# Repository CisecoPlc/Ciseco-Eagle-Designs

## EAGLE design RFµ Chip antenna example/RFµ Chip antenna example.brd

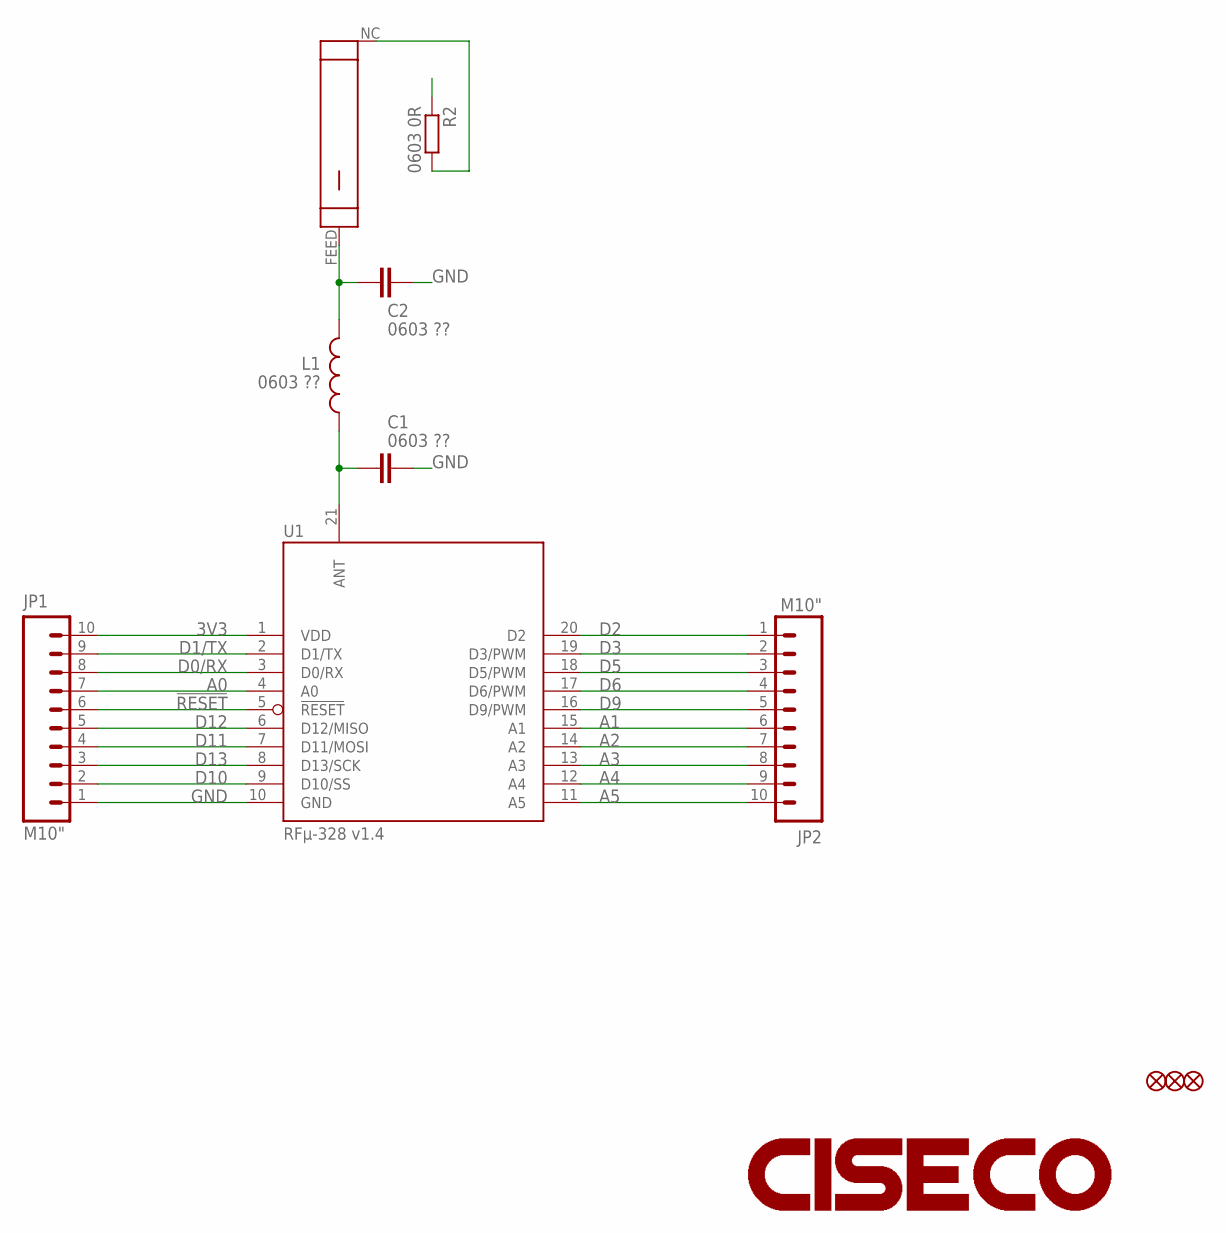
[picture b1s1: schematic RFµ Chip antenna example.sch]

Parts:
C1, C2: 0603 ??; C0603K-SMALL
JP1, JP2: M10"; 1X10
JP3, JP4, JP5: FIDUCIAL1X2.5-STOP; FIDUCIAL-1X2.5-STOP
L1: 0603 ??; C0603K-SMALL
LOGO1: CISECOLOGO-4MM; CISECO-4MM
R2: 0603 0R; C0603K-SMALL
U1: RFµ-328 v1.4; RFµ-LANDING-V2.0
U$1: JTICHIPANT

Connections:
3V3: JP1.10, U1.1 (VDD)
!RESET: JP1.6, U1.5 (!RESET)
A0: JP1.7, U1.4 (A0)
A1: JP2.6, U1.15 (A1)
A2: JP2.7, U1.14 (A2)
A3: JP2.8, U1.13 (A3)
A4: JP2.9, U1.12 (A4)
A5: JP2.10, U1.11 (A5)
ANT: C1.1, L1.1, U1.21 (ANT)
D0/RX: JP1.8, U1.3 (D0/RX)
D1/TX: JP1.9, U1.2 (D1/TX)
D2: JP2.1, U1.20 (D2)
D3: JP2.2, U1.19 (D3/PWM)
D5: JP2.3, U1.18 (D5/PWM)
D6: JP2.4, U1.17 (D6/PWM)
D9: JP2.5, U1.16 (D9/PWM)
D10: JP1.2, U1.9 (D10/SS)
D11: JP1.4, U1.7 (D11/MOSI)
D12: JP1.5, U1.6 (D12/MISO)
D13: JP1.3, U1.8 (D13/SCK)
GND: C1.2, C2.2, JP1.1, U1.10 (GND)
unnamed: C2.1, L1.2, U$1.FEED
unnamed: R2.2, U$1.NC

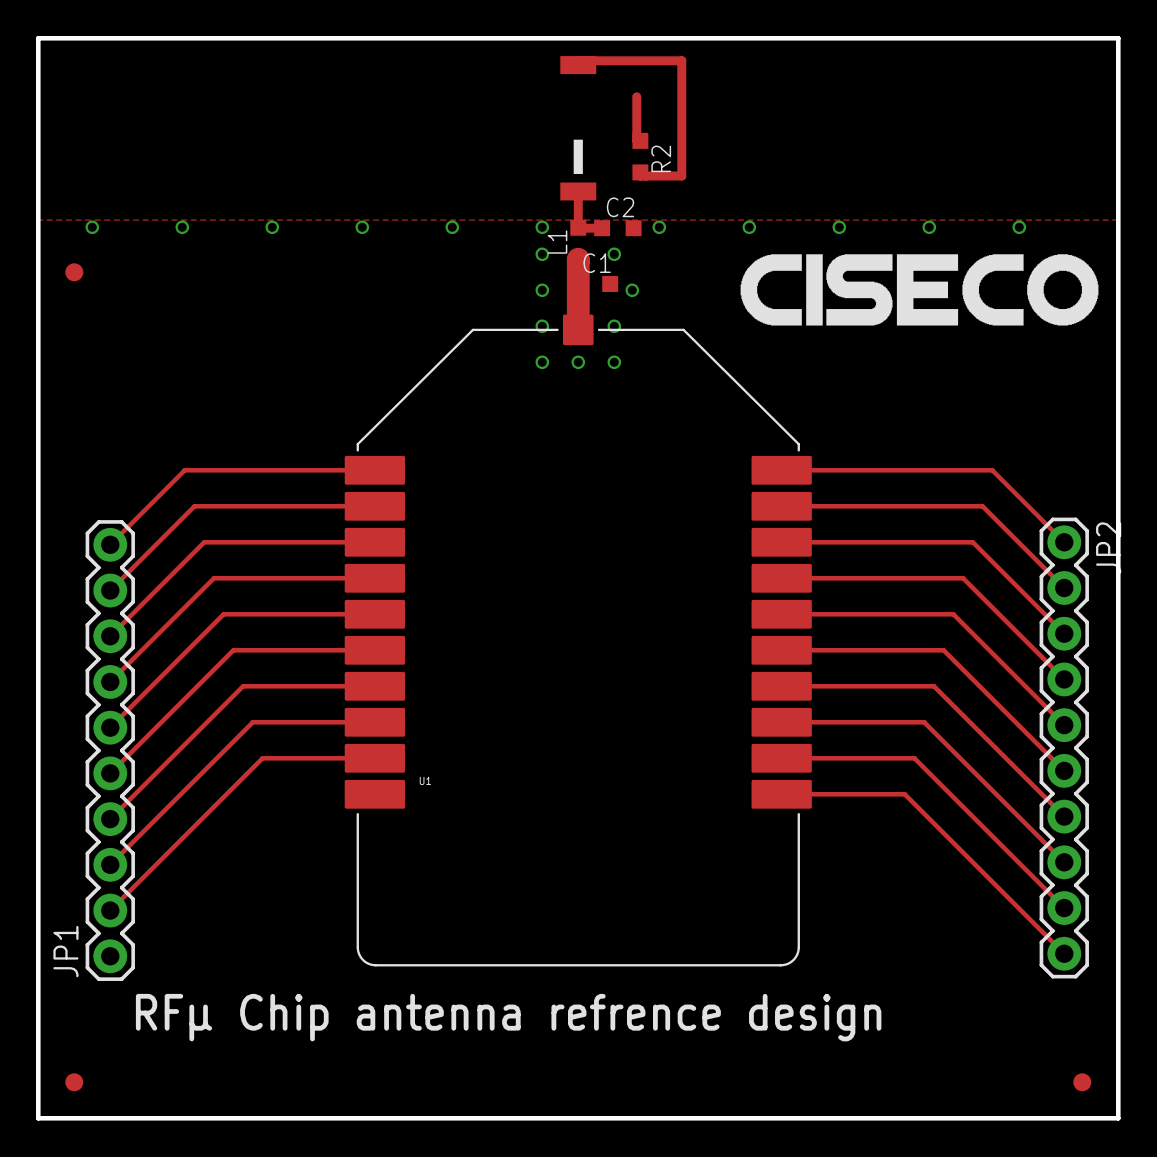
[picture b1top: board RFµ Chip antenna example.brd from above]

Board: 2 copper layers, 60.0 x 60.0 mm, 12 parts (0 on the bottom side), 23 nets.

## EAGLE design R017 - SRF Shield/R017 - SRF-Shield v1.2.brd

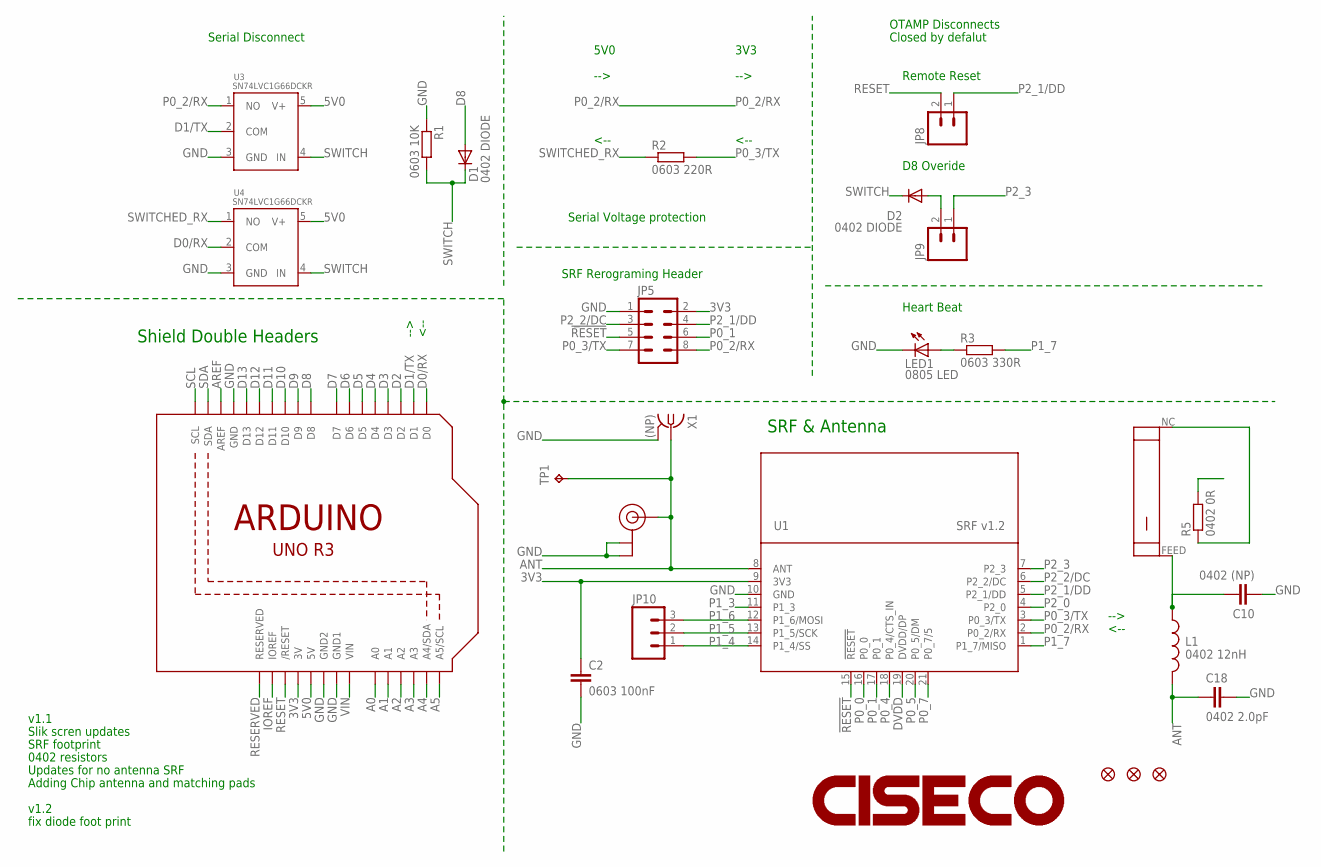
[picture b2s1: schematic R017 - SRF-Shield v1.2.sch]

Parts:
C2: 0603 100nF; C0402-SMALLER
C10: 0402 (NP); C0402-SMALLER
C18: 0402 2.0pF; C0402-SMALLER
D1, D2: 0402 DIODE; SOD88
JP4, JP6, JP7: FIDUCIAL1X2.5-STOP; FIDUCIAL-1X2.5-STOP
JP5: M04X2; 2X4
JP8, JP9: M02PTH; 1X02
JP10: M03PTH; 1X03
L1: 0402 12nH; C0402-SMALLER
LED1: 0805 LED; LED-0805-1206
R1: 0603 10K; R0402-SMALLER
R2: 0603 220R; R0402-SMALLER
R3: 0603 330R; R0402-SMALLER
R5: 0402 0R; R0402-SMALLER
TP1: TPPAD1-13; P1-13
U1: SRF v1.2; SRF-LANDING-NO-ANT-1.2
U2: ARDUINOR3-DOUBL-OFFSET; ARDUINOR3-DOUBLE-OFFSET
U3, U4: SN74LVC1G66DCKR; SC70
U5: U.FL (NP); U.FL
U6: JTICHIPANT; JTICHIPANT-ROT
U$3: CISECO-LARGE; CISECO-4MM
X1: (NP); J502-ND-142-0711-821/826-LWK1

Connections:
3V3: C2.1, JP5.2, U1.9 (3V3), U2.3V, U2.3V1 (3V)
5V0: U2.5V, U2.5V1 (5V), U3.5 (V+), U4.5 (V+)
!RESET: JP5.5, U1.15 (!RESET)
A0: U2.A0, U2.A6 (A0)
A1: U2.A1, U2.A7 (A1)
A2: U2.A2, U2.A8 (A2)
A3: U2.A3, U2.A9 (A3)
A4: U2.A4 (A4/SDA), U2.A10 (A4/SDA)
A5: U2.A5 (A5/SCL), U2.A11 (A5/SCL)
ANT: C18.1, L1.2, TP1.TP, U1.8 (ANT), U5.P$3 (SIGNAL), X1.1
AREF: U2.AREF, U2.AREF1 (AREF)
D0/RX: U2.D0, U2.D18 (D0), U4.2 (COM)
D1/TX: U2.D1, U2.D17 (D1), U3.2 (COM)
D2: U2.D2, U2.D16 (D2)
D3: U2.D3, U2.D15 (D3)
D4: U2.D4, U2.D14 (D4)
D5: U2.D5, U2.D19 (D5)
D6: U2.D6, U2.D20 (D6)
D7: U2.D7, U2.D21 (D7)
D8: D1.A, U2.D8, U2.D22 (D8)
D9: U2.D9, U2.D23 (D9)
D10: U2.D10, U2.D24 (D10)
D11: U2.D11, U2.D25 (D11)
D12: U2.D12, U2.D26 (D12)
D13: U2.D13, U2.D27 (D13)
DVDD: U1.19 (DVDD/DP)
GND: C2.2, C10.1, C18.2, JP5.1, LED1.C, R1.1, U1.10 (GND), U2.GND, U2.GND1, U2.GND2, U2.GND3 (GND1), U2.GND4 (GND2), U2.GND5 (GND), U3.3 (GND), U4.3 (GND), U5.P$1 (GND), U5.P$2 (GND), X1.G@1 (GND), X1.G@2 (GND), X1.G@3 (GND), X1.G@4 (GND)
IOREF: U2.IOREF, U2.IOREF1 (IOREF)
unnamed: LED1.A, R3.1
unnamed: C10.2, L1.1, U6.FEED
unnamed: R5.1, U6.NC
OTAMP_M: D2.A, JP9.2
P0_0: U1.16 (P0_0)
P0_1: JP5.6, U1.17 (P0_1)
P0_2/RX: JP5.8, U1.2 (P0_2/RX), U3.1 (NO)
P0_3/TX: JP5.7, R2.2, U1.3 (P0_3/TX)
P0_4: U1.18 (P0_4/CTS_IN)
P0_5: U1.20 (P0_5/DM)
P0_7: U1.21 (P0_7/5)
P1_3: U1.11 (P1_3)
P1_4: JP10.1, U1.14 (P1_4/SS)
P1_5: JP10.2, U1.13 (P1_5/SCK)
P1_6: JP10.3, U1.12 (P1_6/MOSI)
P1_7: R3.2, U1.1 (P1_7/MISO)
P2_0: U1.4 (P2_0)
P2_1/DD: JP5.4, JP8.1, U1.5 (P2_1/DD)
P2_2/DC: JP5.3, U1.6 (P2_2/DC)
P2_3: JP9.1, U1.7 (P2_3)
RESERVED: U2.RESERVED, U2.RESERVED1 (RESERVED)
RESET: JP8.2, U2.RESET (/RESET), U2.RESET1 (/RESET)
SCL: U2.SCL, U2.SCL1 (SCL)
SDA: U2.SDA, U2.SDA1 (SDA)
SWITCH: D1.C, D2.C, R1.2, U3.4 (IN), U4.4 (IN)
SWITCHED_RX: R2.1, U4.1 (NO)
VIN: U2.VIN, U2.VIN1 (VIN)

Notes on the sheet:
SRF Rerograming Header
5V0
3V3
Remote Reset
Heart Beat
Closed by defalut
OTAMP Disconnects
Serial Voltage protection
Serial Disconnect
<--
-->
D8 Overide
Shield Double Headers
SRF & Antenna
v1.1
Slik scren updates
SRF footprint
0402 resistors
Updates for no antenna SRF
Adding Chip antenna and matching pads
v1.2
fix diode foot print

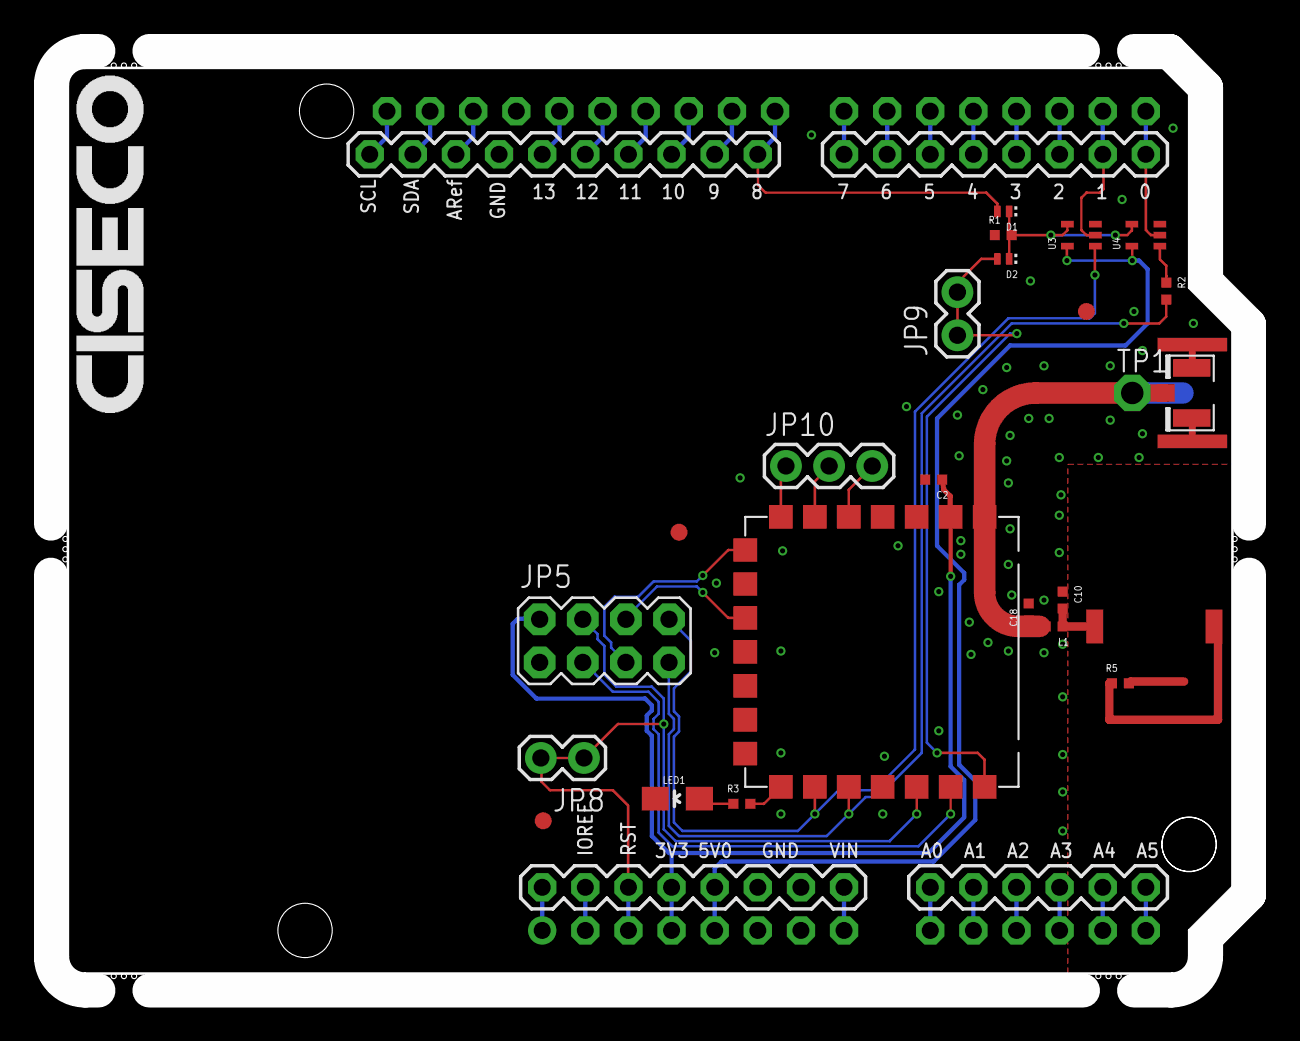
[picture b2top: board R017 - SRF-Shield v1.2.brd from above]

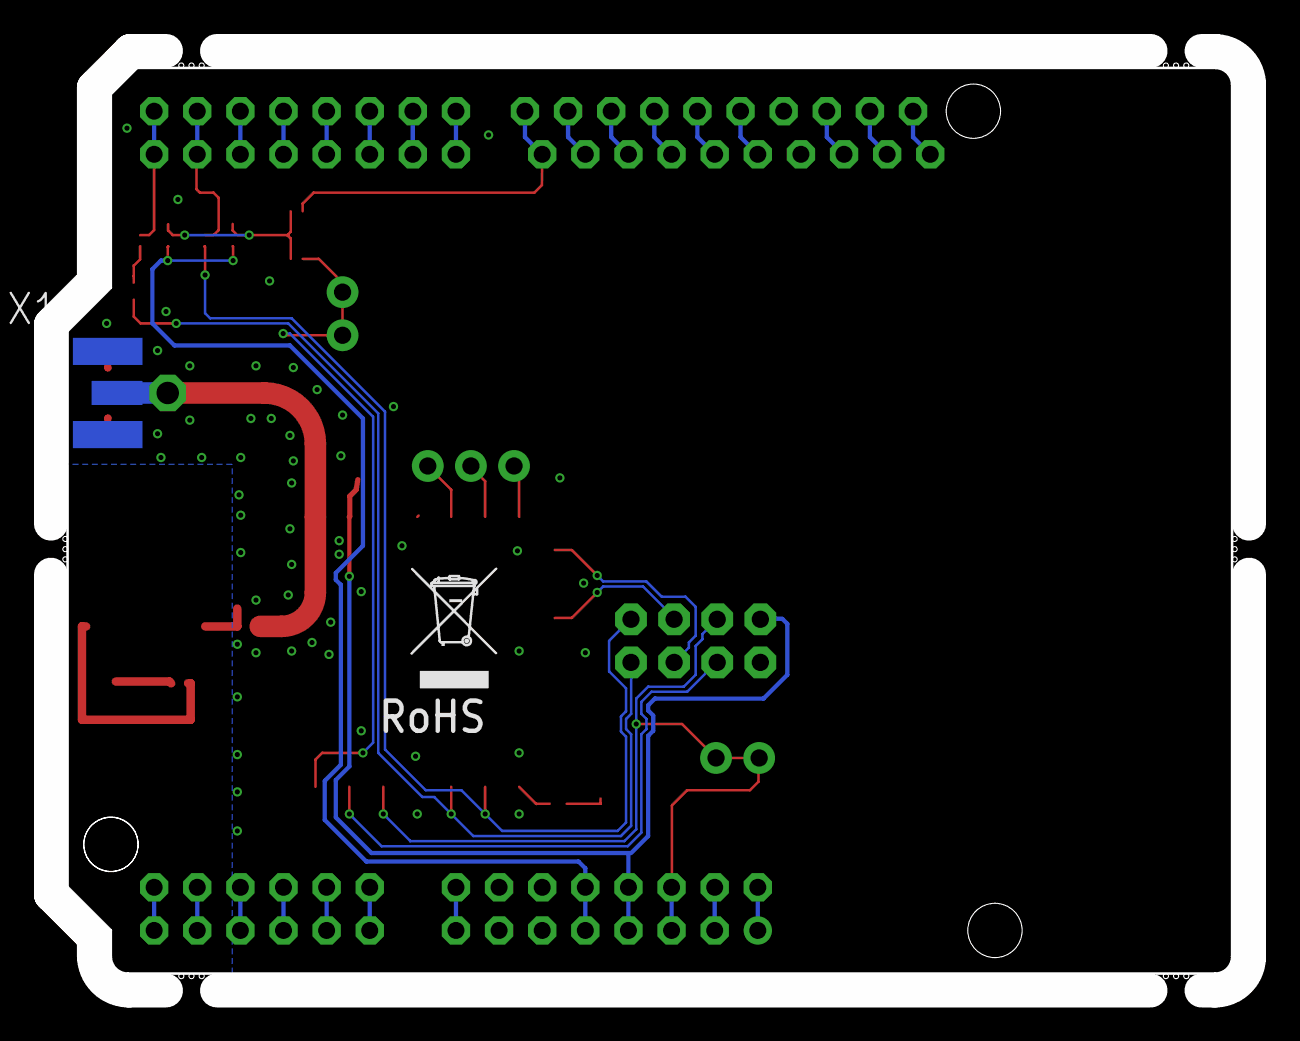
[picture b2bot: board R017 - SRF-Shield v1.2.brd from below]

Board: 2 copper layers, 70.6 x 55.4 mm, 28 parts (2 on the bottom side), 48 nets.

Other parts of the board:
U$6: WEEE-LOGO

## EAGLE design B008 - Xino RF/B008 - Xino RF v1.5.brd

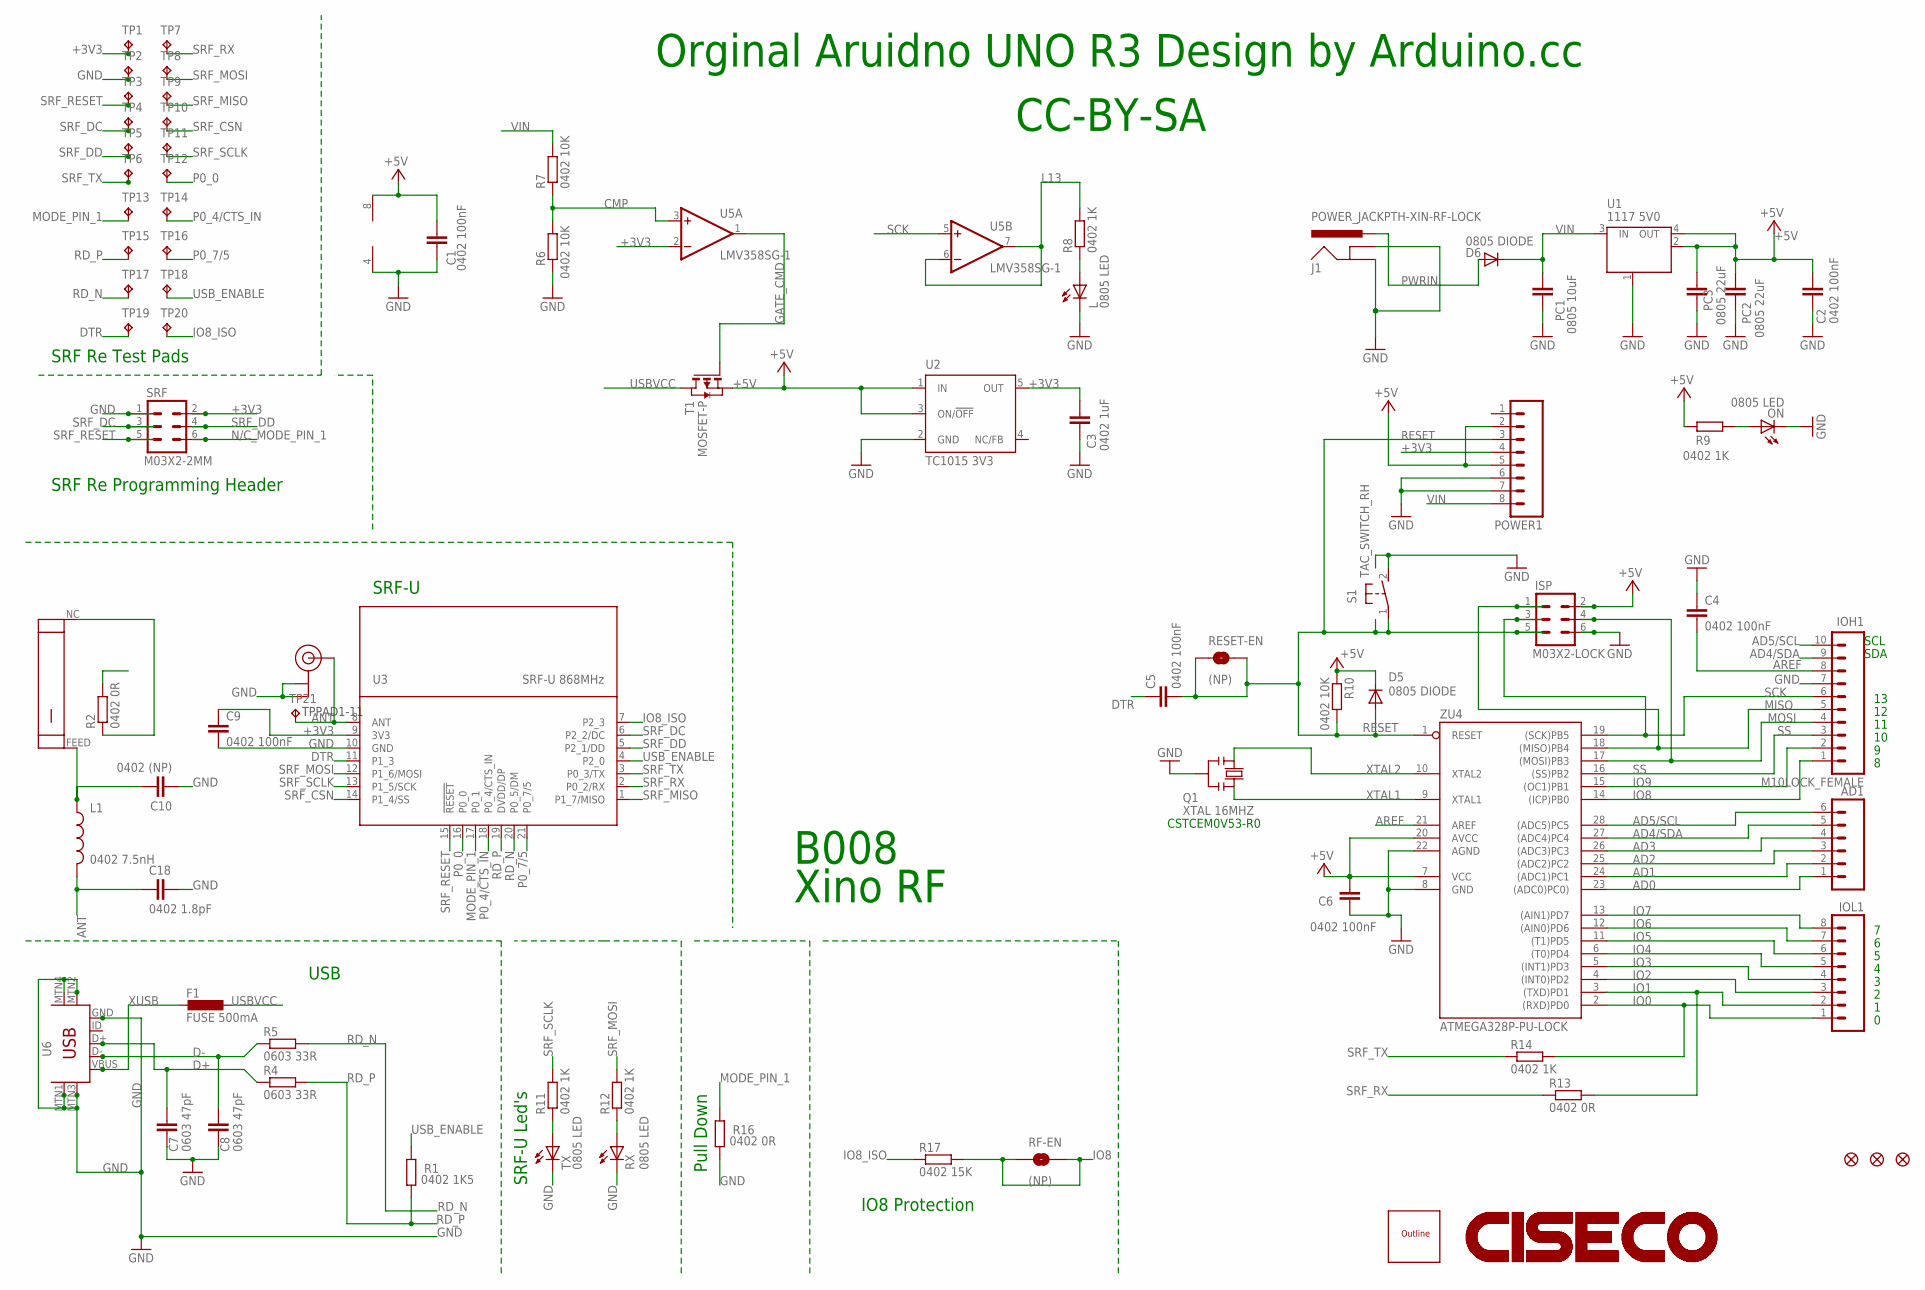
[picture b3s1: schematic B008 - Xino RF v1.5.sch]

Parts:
AD1: M06LOCK_FEMALE; 1X06_LOCK_FEMALE
C1, C2, C4, C5, C9: 0402 100nF; C0402-SMALLER
C3: 0402 1uF; C0402-SMALLER
C6: 0402 100nF; C0603-ROUND
C7, C8: 0603 47pF; C0603K-SMALL
C10: 0402 (NP); C0402-SMALLER
C18: 0402 1.8pF; C0402-SMALLER
D5, D6: 0805 DIODE; 0805-DIODE
F1: FUSE 500mA; L1812
FD1, FD2, FD3: FIDUCIAL1X2.5-STOP; FIDUCIAL-1X2.5-STOP
IOH1: M10LOCK_FEMALE; 1X10_LOCK_FEMALE
IOL1: M08LOCK_FEMALE; 1X08_LOCK_FEMALE
ISP: M03X2-LOCK; 2X3_LOCK
J1: POWER_JACKPTH-XIN-RF-LOCK; POWER_JACK_PTH_XINO_RF_LOCK
L: 0805 LED; LED-0805-1206
L1: 0402 7.5nH; C0402-SMALLER
ON: 0805 LED; LED-0805-1206
PC1: 0805 10uF; C0805K
PC2, PC3: 0805 22uF; C0805K
POWER1: M08LOCK_FEMALE; 1X08_LOCK_FEMALE
Q1: XTAL 16MHZ; RESONATOR
R1: 0402 1K5; R0402-SMALLER
R2, R13, R16: 0402 0R; R0402-SMALLER
R4, R5: 0603 33R; C0603K-SMALL
R6, R7, R10: 0402 10K; R0402-SMALLER
R8, R9, R11, R12, R14: 0402 1K; R0402-SMALLER
R17: 0402 15K; R0402-SMALLER
RESET-EN: (NP); SJ
RF-EN: (NP); SJ
RX: 0805 LED; LED-0805-1206
S1: TAC_SWITCH_RH; B3F-31XX
SRF: M03X2-2MM; 2X3_2MM
T1: MOSFET-P; SOT-23
TP1, TP2, TP3, TP4, TP5, TP6, TP7, TP8, TP9, TP10, TP11, TP12, TP13, TP14, TP15, TP16, TP17, TP18, TP19, TP20: TPB1,27; B1,27
TP21: TPPAD1-11; P1-11
TX: 0805 LED; LED-0805-1206
U1: 1117 5V0; SOT223
U2: TC1015 3V3; SOT23-DBV
U3: SRF-U 868MHz; SRF-LANDING-NO-ANT-1.2
U4: JTICHIPANT; JTICHIPANT-ROT
U5: LMV358SG-1; SO08
U6: USB-MINIB-5PIN; USB-MINIB-CISECO-1
U11: U.FL (NP); U.FL
U$1: CISECO-MEDIUM; CISECO-1.3MM
U$2: ARDUINO-OUTLINE-MILL-VSCORE
U$3: CISECO-LARGE; CISECO-4MM
ZU4: ATMEGA328P-PU-LOCK; DIL28-3-LOCK

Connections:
+3V3: C3.2, C9.1, POWER1.4, SRF.2, TP1.TP, U2.5 (OUT), U3.9 (3V3), U5.2 (-IN)
+5V: C1.2, C2.2, C6.2, D5.C, ISP.2, PC2.1, PC3.1, POWER1.2, POWER1.5, R9.2, R10.1, T1.2 (S), U1.2 (OUT), U1.4 (OUT), U2.1 (IN), U2.3 (ON/!OFF), U5.8 (V+), ZU4.7 (VCC), ZU4.20 (AVCC)
AD0: AD1.1, ZU4.23 ((ADC0)PC0))
AD1: AD1.2, ZU4.24 ((ADC1)PC1)
AD2: AD1.3, ZU4.25 ((ADC2)PC2)
AD3: AD1.4, ZU4.26 ((ADC3)PC3)
AD4/SDA: AD1.5, IOH1.9, ZU4.27 ((ADC4)PC4)
AD5/SCL: AD1.6, IOH1.10, ZU4.28 ((ADC5)PC5)
ANT: C18.1, L1.2, TP21.TP, U3.8 (ANT), U11.P$3 (SIGNAL)
AREF: C4.2, IOH1.8, ZU4.21 (AREF)
CMP: R6.2, R7.1, U5.3 (+IN)
D+: C7.1, R4.1, U6.D+
D-: C8.1, R5.1, U6.D-
DTR: C5.1, TP19.TP, U3.11 (P1_3)
GATE_CMD: T1.3 (G), U5.1 (OUT)
GND: C1.1, C2.1, C3.1, C4.1, C6.1, C7.2, C8.2, C9.2, C10.1, C18.2, IOH1.7, ISP.6, J1.GND, J1.GNDBREAK, L.C, ON.C, PC1.2, PC2.2, PC3.2, POWER1.6, POWER1.7, Q1.2, R6.1, R16.1, RX.C, S1.2 (S), SRF.1, TP2.TP, TX.C, U1.1 (GND/ADJ), U2.2 (GND), U3.10 (GND), U5.4 (V-), U6.GND, U6.MTN1 (MTN2), U6.MTN2 (MTN3), U6.MTN3 (MTN1), U6.MTN4, U11.P$1 (GND), U11.P$2 (GND), ZU4.8 (GND), ZU4.22 (AGND)
IO0: IOL1.1, R14.2, ZU4.2 ((RXD)PD0)
IO1: IOL1.2, R13.2, ZU4.3 ((TXD)PD1)
IO2: IOL1.3, ZU4.4 ((INT0)PD2)
IO3: IOL1.4, ZU4.5 ((INT1)PD3)
IO4: IOL1.5, ZU4.6 ((T0)PD4)
IO5: IOL1.6, ZU4.11 ((T1)PD5)
IO6: IOL1.7, ZU4.12 ((AIN0)PD6)
IO7: IOL1.8, ZU4.13 ((AIN1)PD7)
IO8: IOH1.1, R17.2, RF-EN.1, RF-EN.2, ZU4.14 ((ICP)PB0)
IO8_ISO: R17.1, TP20.TP, U3.7 (P2_3)
IO9: IOH1.2, ZU4.15 ((OC1)PB1)
L13: R8.2, U5.6 (-IN), U5.7 (OUT)
MISO: IOH1.5, ISP.1, ZU4.18 ((MISO)PB4)
MODE_PIN_1: R16.2, TP13.TP, U3.17 (P0_1)
MOSI: IOH1.4, ISP.4, ZU4.17 ((MOSI)PB3)
unnamed: L.A, R8.1
unnamed: ON.A, R9.1
unnamed: R12.1, RX.A
unnamed: R11.1, TX.A
unnamed: C10.2, L1.1, U4.FEED
unnamed: R2.1, U4.NC
N/C_MODE_PIN_1: SRF.6
P0_0: TP12.TP, U3.16 (P0_0)
P0_4/CTS_IN: TP14.TP, U3.18 (P0_4/CTS_IN)
P0_7/5: TP16.TP, U3.21 (P0_7/5)
PWRIN: D6.A, J1.PWR
RD_N: R5.2, TP17.TP, U3.20 (P0_5/DM)
RD_P: R1.1, R4.2, TP15.TP, U3.19 (DVDD/DP)
RESET: C5.2, D5.A, ISP.5, POWER1.3, R10.2, RESET-EN.1, RESET-EN.2, S1.1, ZU4.1 (RESET)
SCK: IOH1.6, ISP.3, U5.5 (+IN), ZU4.19 ((SCK)PB5)
SRF_CSN: TP10.TP, U3.14 (P1_4/SS)
SRF_DC: SRF.3, TP4.TP, U3.6 (P2_2/DC)
SRF_DD: SRF.4, TP5.TP, U3.5 (P2_1/DD)
SRF_MISO: TP9.TP, U3.1 (P1_7/MISO)
SRF_MOSI: R12.2, TP8.TP, U3.12 (P1_6/MOSI)
SRF_RESET: SRF.5, TP3.TP, U3.15 (!RESET)
SRF_RX: R13.1, TP7.TP, U3.2 (P0_2/RX)
SRF_SCLK: R11.2, TP11.TP, U3.13 (P1_5/SCK)
SRF_TX: R14.1, TP6.TP, U3.3 (P0_3/TX)
SS: IOH1.3, ZU4.16 ((SS)PB2)
USBVCC: F1.1, T1.1 (D)
USB_ENABLE: R1.2, TP18.TP, U3.4 (P2_0)
VIN: D6.C, PC1.1, POWER1.8, R7.2, U1.3 (IN)
XTAL1: Q1.3, ZU4.9 (XTAL1)
XTAL2: Q1.1, ZU4.10 (XTAL2)
XUSB: F1.2, U6.VBUS

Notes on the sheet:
Xino RF
SDA
SCL
Pull Down
IO8 Protection
CC-BY-SA
Orginal Aruidno UNO R3 Design by Arduino.cc
USB
SRF Re Programming Header
SRF Re Test Pads
SRF-U
SRF-U Led's
B008
CSTCEM0V53-R0

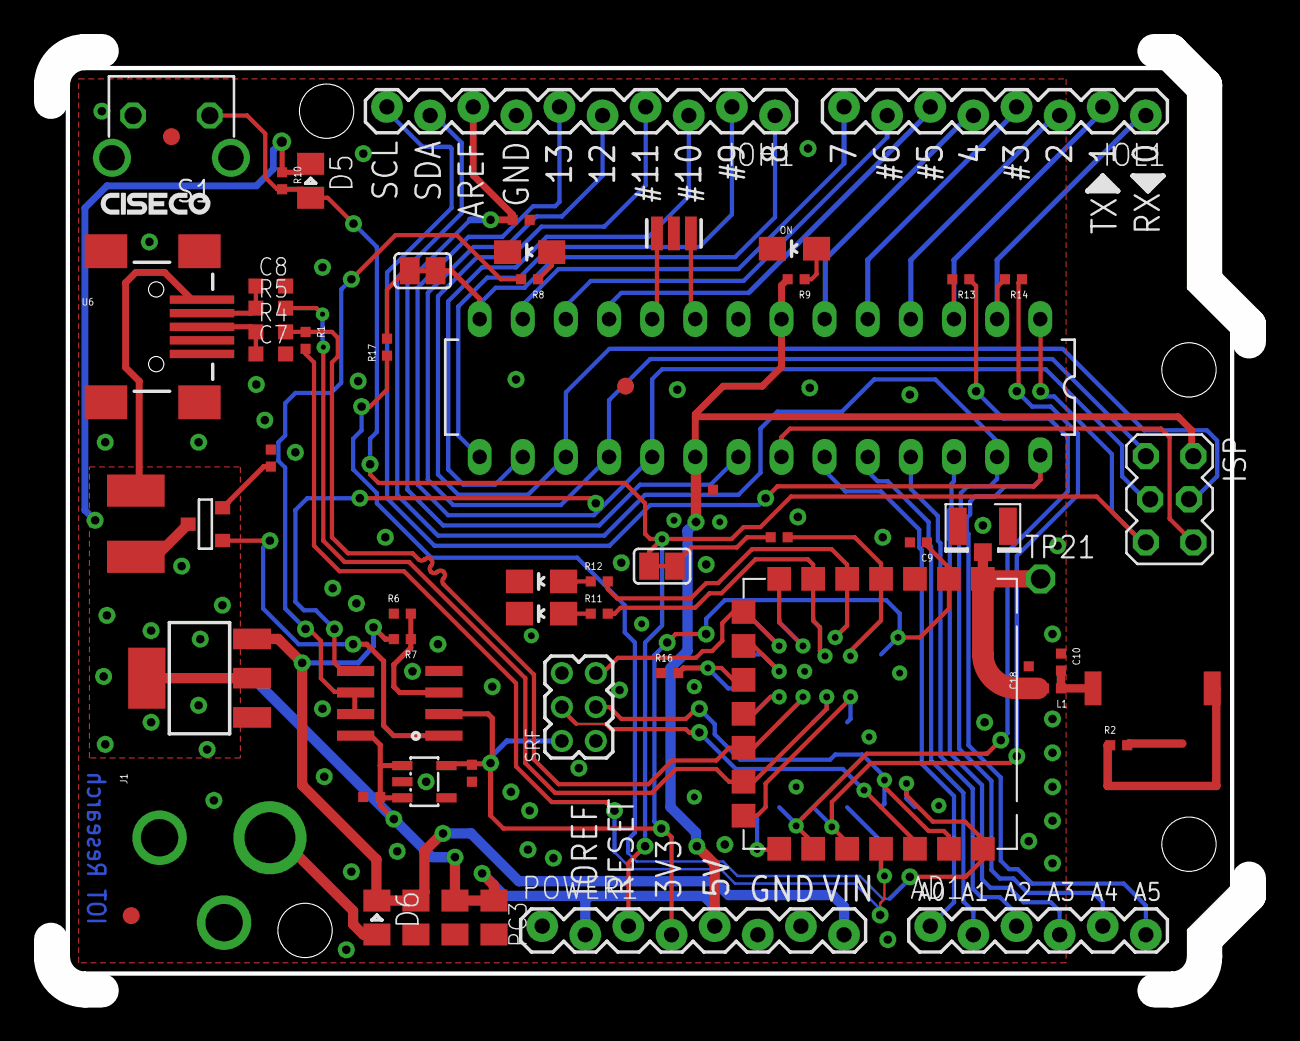
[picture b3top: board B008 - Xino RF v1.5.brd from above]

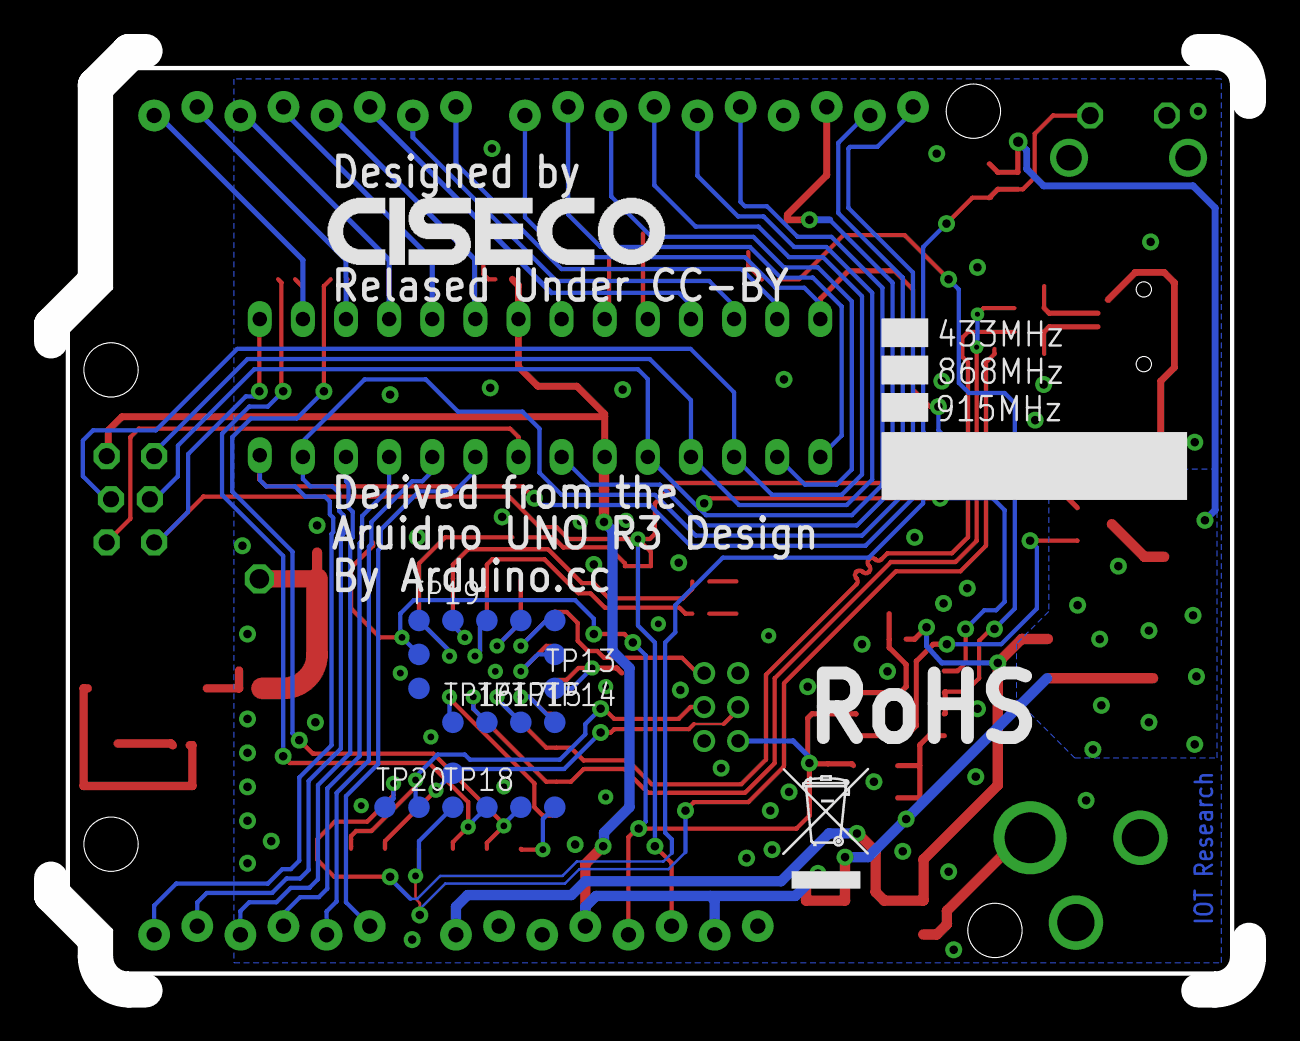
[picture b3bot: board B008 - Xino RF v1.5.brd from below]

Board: 2 copper layers, 70.6 x 55.4 mm, 85 parts (22 on the bottom side), 61 nets.

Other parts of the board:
U$4: WEEE-LOGO

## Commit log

2014-05-28 Committing R016 R017 and B008 files
2014-05-28 Adding Readme
2014-09-23 Adding RFµ chip antenna example design

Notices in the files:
B008 - Xino RF/B008 - Xino RF v1.5.brd:
Relased Under CC-BY
